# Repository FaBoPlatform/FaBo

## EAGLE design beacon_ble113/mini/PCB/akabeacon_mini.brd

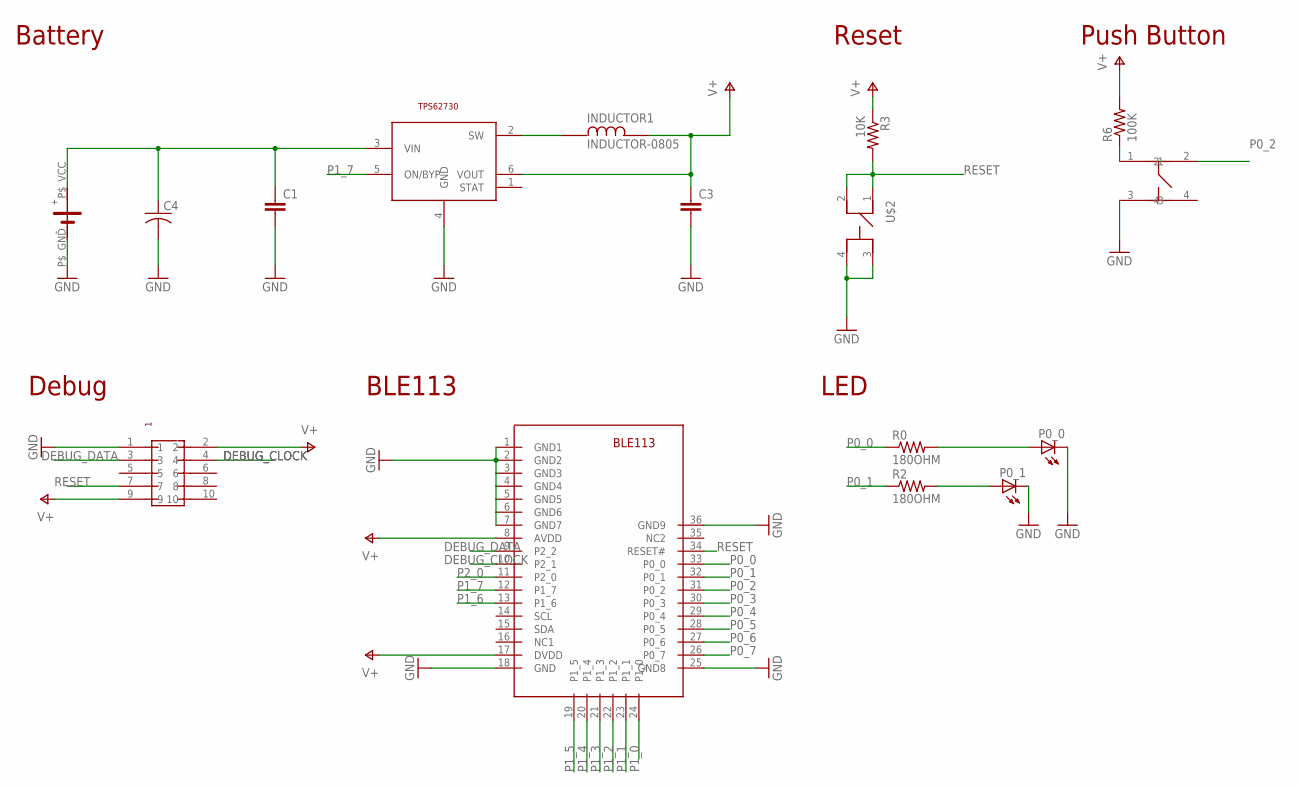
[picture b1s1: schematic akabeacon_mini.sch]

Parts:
C1, C3: C-EUC0603; C0603
C4: C-USC3225; C3225
INDUCTOR1: INDUCTOR-0805
P0_0, P0_1: LEDCHIP-LED0603; CHIP-LED0603
R0, R2: 180OHM; 0603-RES
R3: 10K; 0603-RES
R6: 100K; 0603-RES
TPS1: TI-TPS62730
U$1: SMTU2450-BOTTOM-MINI
U$2: SWITCH-LS6J2M-T
U$3: PIN-HEADER-SMT(1.27MM)2X5
U$4: BLE113
U$5: SWICTH-4P(KMR2); SWITCH-4P(KMR2)

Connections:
DEBUG_CLOCK: U$3.4, U$4.10 (P2_1)
DEBUG_DATA: U$3.3, U$4.9 (P2_2)
GND: C1.2, C3.2, C4.2, P0_0.C, P0_1.C, TPS1.4 (GND), U$1.P$_GND, U$2.3, U$2.4, U$3.1, U$4.1 (GND1), U$4.2 (GND2), U$4.3 (GND3), U$4.4 (GND4), U$4.5 (GND5), U$4.6 (GND6), U$4.7 (GND7), U$4.18 (GND), U$4.25 (GND8), U$4.36 (GND9), U$5.3
unnamed: C1.1, C4.1, TPS1.3 (VIN), U$1.P$_VCC
unnamed: P0_0.A, R0.2
unnamed: P0_1.A, R2.2
unnamed: INDUCTOR1.P$1, TPS1.2 (SW)
P0_0: R0.1, U$4.33 (P0_0)
P0_1: R2.1, U$4.32 (P0_1)
P0_2: R6.1, U$4.31 (P0_2), U$5.1
P0_3: U$4.30 (P0_3)
P0_4: U$4.29 (P0_4)
P0_5: U$4.28 (P0_5)
P0_6: U$4.27 (P0_6)
P0_7: U$4.26 (P0_7)
P1_0: U$4.24 (P1_0)
P1_1: U$4.23 (P1_1)
P1_2: U$4.22 (P1_2)
P1_3: U$4.21 (P1_3)
P1_4: U$4.20 (P1_4)
P1_5: U$4.19 (P1_5)
P1_6: U$4.13 (P1_6)
P1_7: TPS1.5 (ON/BYP), U$4.12 (P1_7)
P2_0: U$4.11 (P2_0)
RESET: R3.2, U$2.1, U$3.7, U$4.34 (RESET#)
V+: C3.1, INDUCTOR1.P$2, R3.1, R6.2, TPS1.6 (VOUT), U$3.2, U$3.9, U$4.8 (AVDD), U$4.17 (DVDD)

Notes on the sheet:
Reset
Battery
Push Button
Debug
BLE113
LED

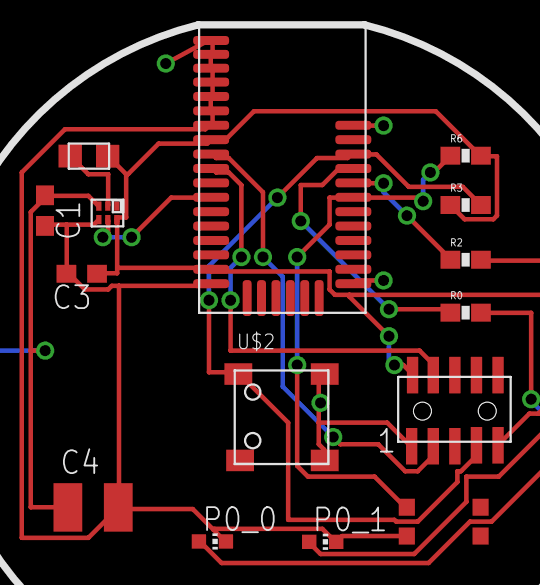
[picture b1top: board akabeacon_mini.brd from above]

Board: 2 copper layers, 16 parts (0 on the bottom side), 13 nets.

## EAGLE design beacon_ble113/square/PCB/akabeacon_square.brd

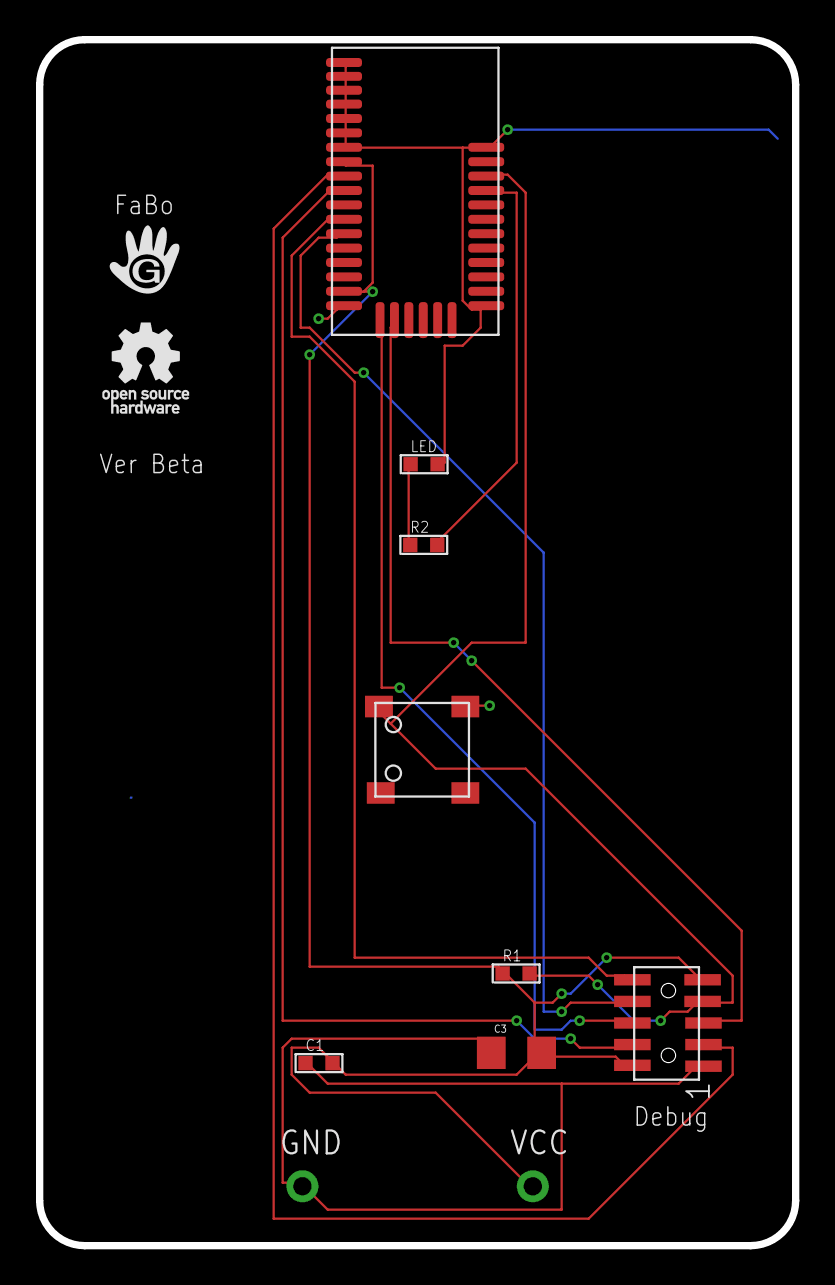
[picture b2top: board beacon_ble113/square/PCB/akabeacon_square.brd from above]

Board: 4 copper layers, 42.0 x 67.0 mm, 12 parts (0 on the bottom side), 11 nets.

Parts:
C1: 1u; 0603
C3: 100uF; 1206
GND: 1X01-CLEANBIG
LED: LED0603; 0603
R1, R2: 4.7K; 0603
U$2: PIN-HEADER-SMT(1.27MM)2X5
U$3: LOGO_FABO_M
U$4: LOGO_OSHW_T_M
U$5: BLE113
U$8: SWITCH-LS6J2M-T; SWICTH-LS6J2M-T
VCC: 1X01-CLEANBIG

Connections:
3.3V: C1.2, C3.2, R1.1, U$2.2, U$2.9, U$5.8, U$5.17, VCC.1
DEBUG_CLOCK: U$2.4, U$5.10
DEBUG_DATA: U$2.3, U$5.9
GND: C1.1, C3.1, GND.1, LED.CATHODE, U$2.1, U$5.1, U$5.2, U$5.3, U$5.4, U$5.5, U$5.6, U$5.7, U$5.18, U$5.25, U$5.36, U$8.3
unnamed: LED.ANODE, R2.1
P0_0: R2.2, U$5.33
P1_4: U$2.5, U$5.20
P1_5: U$2.6, U$5.19
P1_6: U$2.8, U$5.13
P1_7: U$2.10, U$5.12
RESET: R1.2, U$2.7, U$5.34, U$8.1

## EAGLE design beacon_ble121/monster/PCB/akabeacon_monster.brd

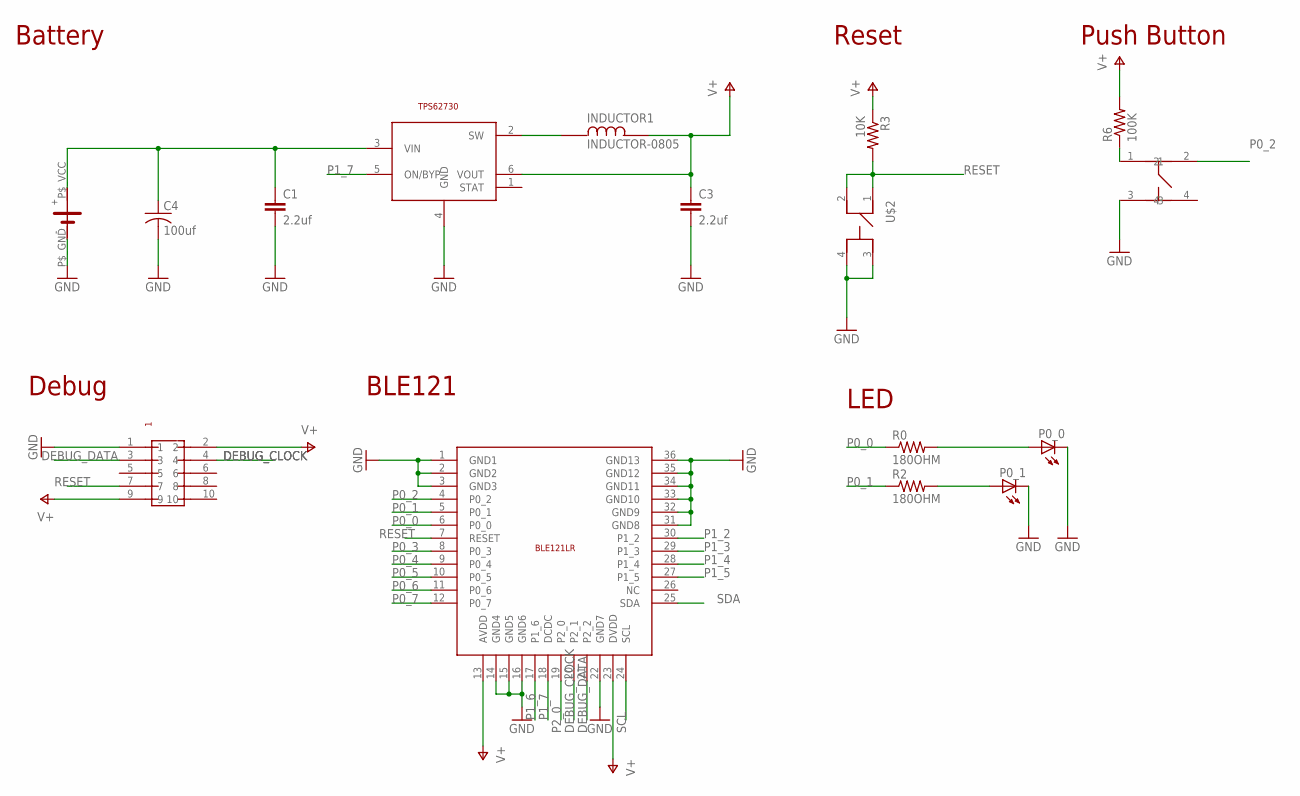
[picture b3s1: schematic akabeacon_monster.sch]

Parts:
BLE1: BLUEGIGA-BLE121LR
C1, C3: 2.2uf; C0603
C4: 100uf; C3225
INDUCTOR1: INDUCTOR-0805
P0_0, P0_1: LEDCHIP-LED0603; CHIP-LED0603
R0, R2: 180OHM; 0603-RES
R3: 10K; 0603-RES
R6: 100K; 0603-RES
TPS1: TI-TPS62730
U$1: SMTU2450-BOTTOM-MINI
U$2: SWITCH-LS6J2M-T
U$3: PIN-HEADER-SMT(1.27MM)2X5
U$5: SWICTH-4P(KMR2); SWITCH-4P(KMR2)

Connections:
DEBUG_CLOCK: BLE1.20 (P2_1), U$3.4
DEBUG_DATA: BLE1.21 (P2_2), U$3.3
GND: BLE1.1 (GND1), BLE1.2 (GND2), BLE1.3 (GND3), BLE1.22 (GND7), BLE1.31 (GND8), BLE1.32 (GND9), BLE1.33 (GND10), BLE1.34 (GND11), BLE1.35 (GND12), BLE1.36 (GND13), C1.2, C3.2, C4.2, P0_0.C, P0_1.C, TPS1.4 (GND), U$1.P$_GND, U$2.3, U$2.4, U$3.1, U$5.3
unnamed: C1.1, C4.1, TPS1.3 (VIN), U$1.P$_VCC
unnamed: P0_0.A, R0.2
unnamed: P0_1.A, R2.2
unnamed: INDUCTOR1.P$1, TPS1.2 (SW)
unnamed: BLE1.14 (GND4), BLE1.15 (GND5), BLE1.16 (GND6)
P0_0: BLE1.6 (P0_0), R0.1
P0_1: BLE1.5 (P0_1), R2.1
P0_2: BLE1.4 (P0_2), R6.1, U$5.1
P0_3: BLE1.8 (P0_3)
P0_4: BLE1.9 (P0_4)
P0_5: BLE1.10 (P0_5)
P0_6: BLE1.11 (P0_6)
P0_7: BLE1.12 (P0_7)
P1_2: BLE1.30 (P1_2)
P1_3: BLE1.29 (P1_3)
P1_4: BLE1.28 (P1_4)
P1_5: BLE1.27 (P1_5)
P1_6: BLE1.17 (P1_6)
P1_7: BLE1.18 (DCDC), TPS1.5 (ON/BYP)
P2_0: BLE1.19 (P2_0)
RESET: BLE1.7 (RESET), R3.2, U$2.1, U$2.2, U$3.7
SCL: BLE1.24 (SCL)
SDA: BLE1.25 (SDA)
V+: BLE1.13 (AVDD), BLE1.23 (DVDD), C3.1, INDUCTOR1.P$2, R3.1, R6.2, TPS1.6 (VOUT), U$3.2, U$3.9

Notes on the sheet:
Reset
Battery
Push Button
Debug
BLE121
LED

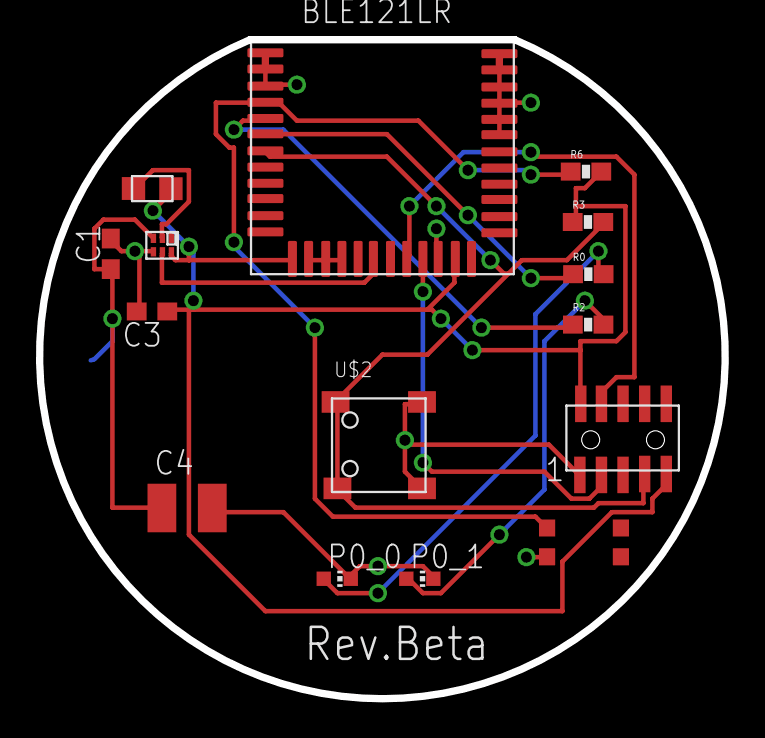
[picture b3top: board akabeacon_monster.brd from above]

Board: 2 copper layers, 38.1 x 36.6 mm, 16 parts (0 on the bottom side), 14 nets.

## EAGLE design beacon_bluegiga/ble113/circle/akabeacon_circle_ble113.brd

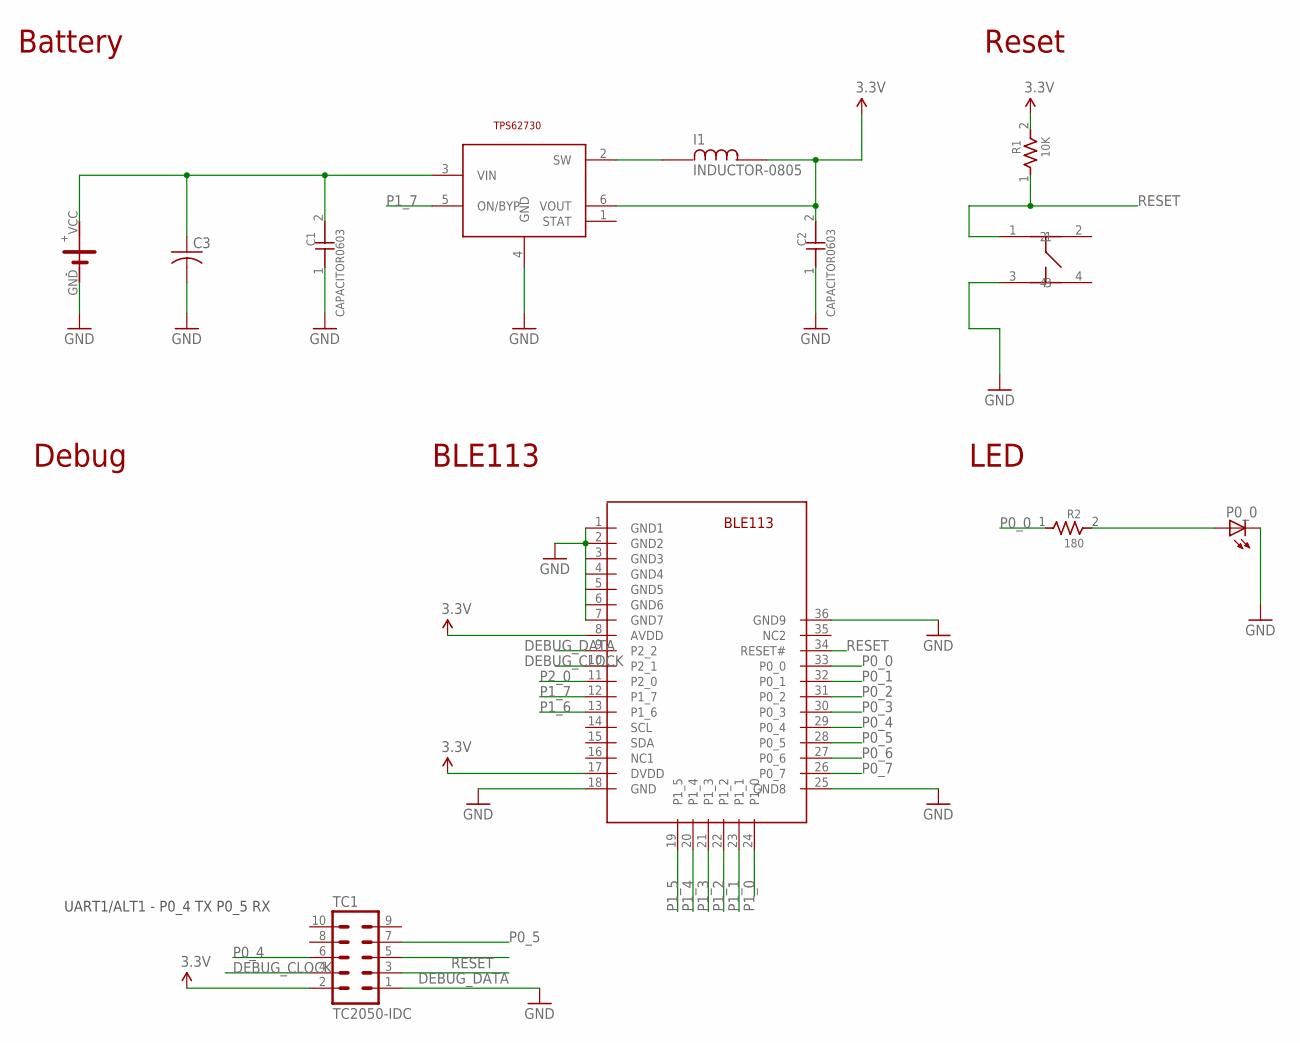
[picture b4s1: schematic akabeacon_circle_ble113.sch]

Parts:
C1, C2: CAPACITOR0603; 0603
C3: C-USC3225; C3225
I1: INDUCTOR-0805
P0_0: LEDCHIP-LED0603; CHIP-LED0603
R1: 10K; 0603
R2: 180; 0603
TC1: TC2050-IDC; TC2050-IDC-NL
TPS1: TI-TPS62730
U$1: CIRCLE-TYPE1; CIRCLE-TYE1-TC2030
U$4: BLE113
U$5: SWICTH-4P(KMR2); SWITCH-4P(KMR2)

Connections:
3.3V: C2.2, I1.P$2, R1.2, TC1.2, TPS1.6 (VOUT), U$4.8 (AVDD), U$4.17 (DVDD)
DEBUG_CLOCK: TC1.4, U$4.10 (P2_1)
DEBUG_DATA: TC1.3, U$4.9 (P2_2)
GND: C1.1, C2.1, C3.2, P0_0.C, TC1.1, TPS1.4 (GND), U$1.GND, U$4.1 (GND1), U$4.2 (GND2), U$4.3 (GND3), U$4.4 (GND4), U$4.5 (GND5), U$4.6 (GND6), U$4.7 (GND7), U$4.18 (GND), U$4.25 (GND8), U$4.36 (GND9), U$5.3
unnamed: C1.2, C3.1, TPS1.3 (VIN), U$1.VCC
unnamed: I1.P$1, TPS1.2 (SW)
P0_0: R2.1, U$4.33 (P0_0)
P0_1: U$4.32 (P0_1)
P0_2: U$4.31 (P0_2)
P0_3: U$4.30 (P0_3)
P0_4: TC1.6, U$4.29 (P0_4)
P0_5: TC1.7, U$4.28 (P0_5)
P0_6: U$4.27 (P0_6)
P0_7: U$4.26 (P0_7)
P1_0: U$4.24 (P1_0)
P1_1: U$4.23 (P1_1)
P1_2: U$4.22 (P1_2)
P1_3: U$4.21 (P1_3)
P1_4: U$4.20 (P1_4)
P1_5: U$4.19 (P1_5)
P1_6: U$4.13 (P1_6)
P1_7: TPS1.5 (ON/BYP), U$4.12 (P1_7)
P2_0: U$4.11 (P2_0)
R2: P0_0.A, R2.2
RESET: R1.1, TC1.5, U$4.34 (RESET#), U$5.1

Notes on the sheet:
Reset
Battery
Debug
BLE113
LED
UART1/ALT1 - P0_4 TX P0_5 RX

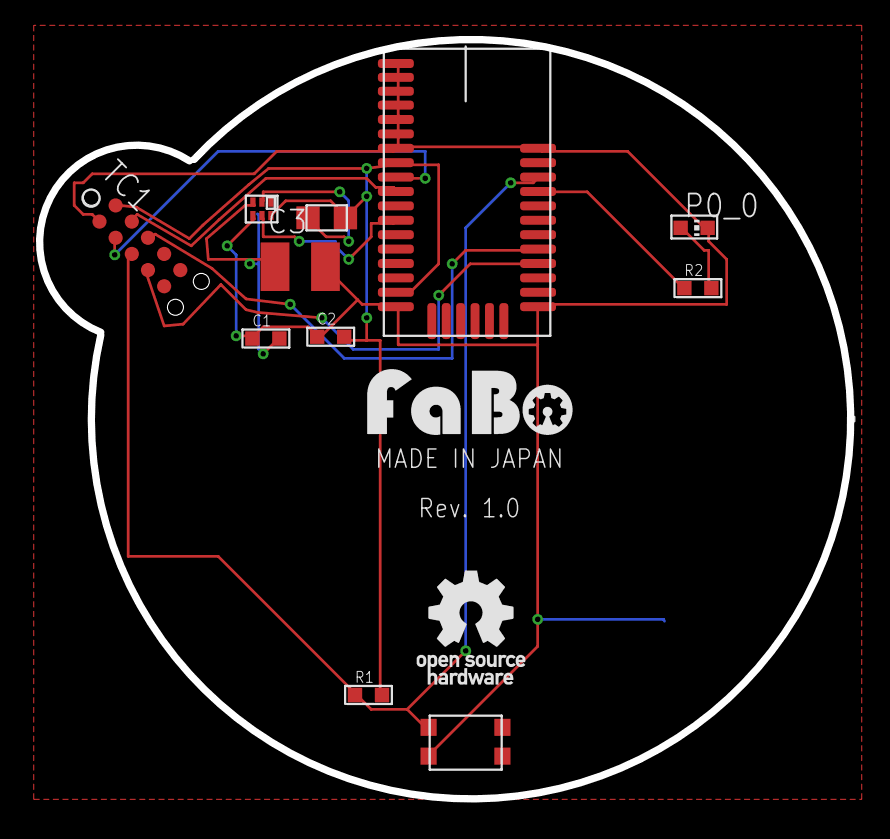
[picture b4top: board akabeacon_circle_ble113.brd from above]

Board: 2 copper layers, 14 parts (0 on the bottom side), 12 nets.

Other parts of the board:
U$2: LOGO_FABO_M
U$7: LOGO_OSHW_T_M

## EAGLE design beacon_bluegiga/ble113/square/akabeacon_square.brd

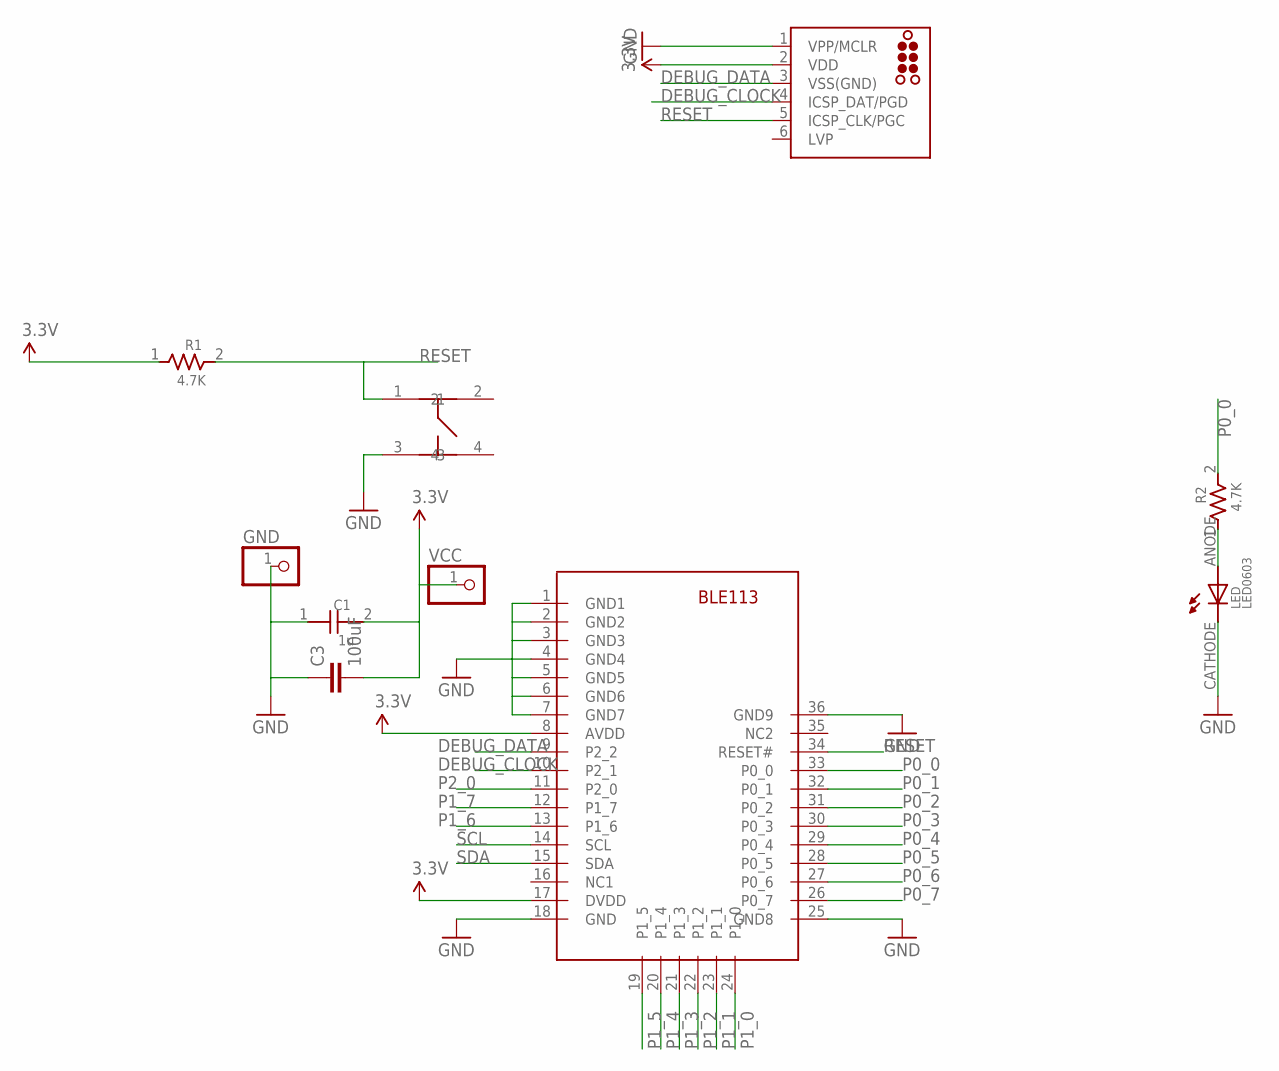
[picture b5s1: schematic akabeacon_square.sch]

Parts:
C1: 1u; 0603
C3: 100uF; 1206
GND: PINHD-1X1CB; 1X01-CLEANBIG
J1: TC2030-MCP
LED: LED0603; 0603
R1, R2: 4.7K; 0603
U$5: BLE113
U$6: SWICTH-4P(KMR2); SWITCH-4P(KMR2)
VCC: PINHD-1X1CB; 1X01-CLEANBIG

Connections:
3.3V: C1.2, C3.2, J1.2 (VDD), R1.1, U$5.8 (AVDD), U$5.17 (DVDD), VCC.1
DEBUG_CLOCK: J1.4 (ICSP_DAT/PGD), U$5.10 (P2_1)
DEBUG_DATA: J1.3 (VSS(GND)), U$5.9 (P2_2)
GND: C1.1, C3.1, GND.1, J1.1 (VPP/MCLR), LED.CATHODE, U$5.1 (GND1), U$5.2 (GND2), U$5.3 (GND3), U$5.4 (GND4), U$5.5 (GND5), U$5.6 (GND6), U$5.7 (GND7), U$5.18 (GND), U$5.25 (GND8), U$5.36 (GND9), U$6.3
unnamed: LED.ANODE, R2.1
P0_0: R2.2, U$5.33 (P0_0)
P0_1: U$5.32 (P0_1)
P0_2: U$5.31 (P0_2)
P0_3: U$5.30 (P0_3)
P0_4: U$5.29 (P0_4)
P0_5: U$5.28 (P0_5)
P0_6: U$5.27 (P0_6)
P0_7: U$5.26 (P0_7)
P1_0: U$5.24 (P1_0)
P1_1: U$5.23 (P1_1)
P1_2: U$5.22 (P1_2)
P1_3: U$5.21 (P1_3)
P1_4: U$5.20 (P1_4)
P1_5: U$5.19 (P1_5)
P1_6: U$5.13 (P1_6)
P1_7: U$5.12 (P1_7)
P2_0: U$5.11 (P2_0)
RESET: J1.5 (ICSP_CLK/PGC), R1.2, U$5.34 (RESET#), U$6.1
SCL: U$5.14 (SCL)
SDA: U$5.15 (SDA)

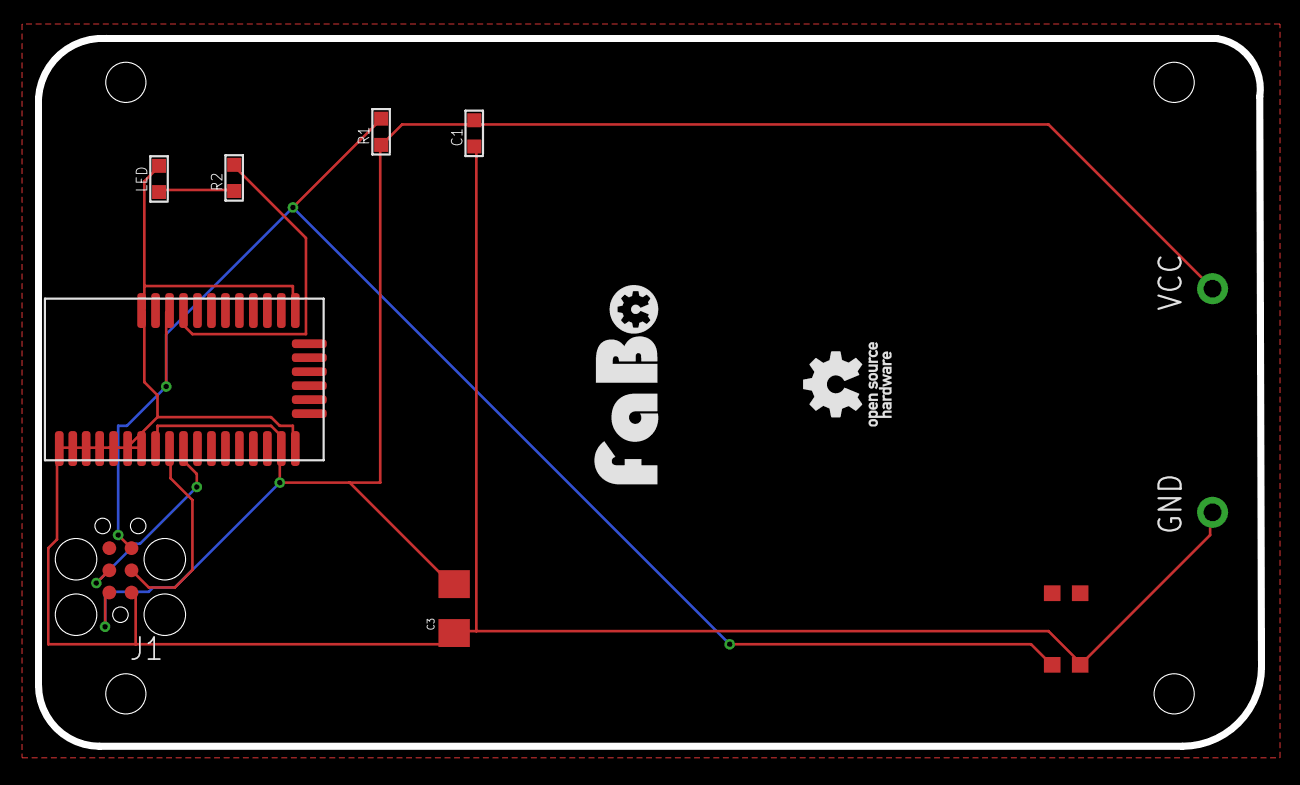
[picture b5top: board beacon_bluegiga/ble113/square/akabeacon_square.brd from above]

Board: 2 copper layers, 70.0 x 40.5 mm, 12 parts (0 on the bottom side), 7 nets.

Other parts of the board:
U$3: LOGO_FABO_M
U$4: LOGO_OSHW_T_M

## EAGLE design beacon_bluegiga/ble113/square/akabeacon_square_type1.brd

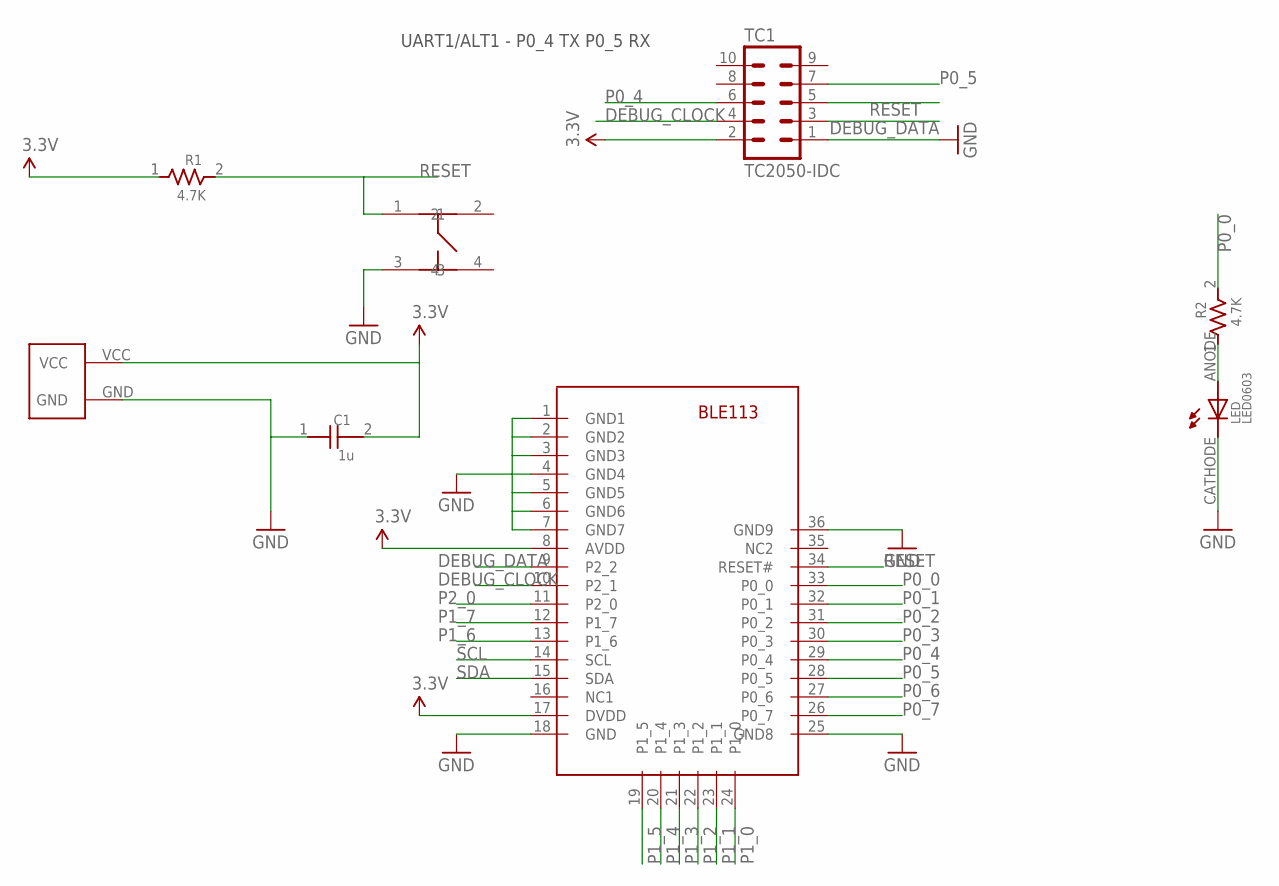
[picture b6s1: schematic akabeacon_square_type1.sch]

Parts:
C1: 1u; 0603
LED: LED0603; 0603
R1, R2: 4.7K; 0603
TC1: TC2050-IDC; TC2050-IDC-NL
U$2: SQUARE-TYPE1; SQUARE-TYPE1-TC2030
U$5: BLE113
U$6: SWICTH-4P(KMR2); SWITCH-4P(KMR2)

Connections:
3.3V: C1.2, R1.1, TC1.2, U$2.VCC, U$5.8 (AVDD), U$5.17 (DVDD)
DEBUG_CLOCK: TC1.4, U$5.10 (P2_1)
DEBUG_DATA: TC1.3, U$5.9 (P2_2)
GND: C1.1, LED.CATHODE, TC1.1, U$2.GND, U$5.1 (GND1), U$5.2 (GND2), U$5.3 (GND3), U$5.4 (GND4), U$5.5 (GND5), U$5.6 (GND6), U$5.7 (GND7), U$5.18 (GND), U$5.25 (GND8), U$5.36 (GND9), U$6.3
unnamed: LED.ANODE, R2.1
P0_0: R2.2, U$5.33 (P0_0)
P0_1: U$5.32 (P0_1)
P0_2: U$5.31 (P0_2)
P0_3: U$5.30 (P0_3)
P0_4: TC1.6, U$5.29 (P0_4)
P0_5: TC1.7, U$5.28 (P0_5)
P0_6: U$5.27 (P0_6)
P0_7: U$5.26 (P0_7)
P1_0: U$5.24 (P1_0)
P1_1: U$5.23 (P1_1)
P1_2: U$5.22 (P1_2)
P1_3: U$5.21 (P1_3)
P1_4: U$5.20 (P1_4)
P1_5: U$5.19 (P1_5)
P1_6: U$5.13 (P1_6)
P1_7: U$5.12 (P1_7)
P2_0: U$5.11 (P2_0)
RESET: R1.2, TC1.5, U$5.34 (RESET#), U$6.1
SCL: U$5.14 (SCL)
SDA: U$5.15 (SDA)

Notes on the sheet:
UART1/ALT1 - P0_4 TX P0_5 RX

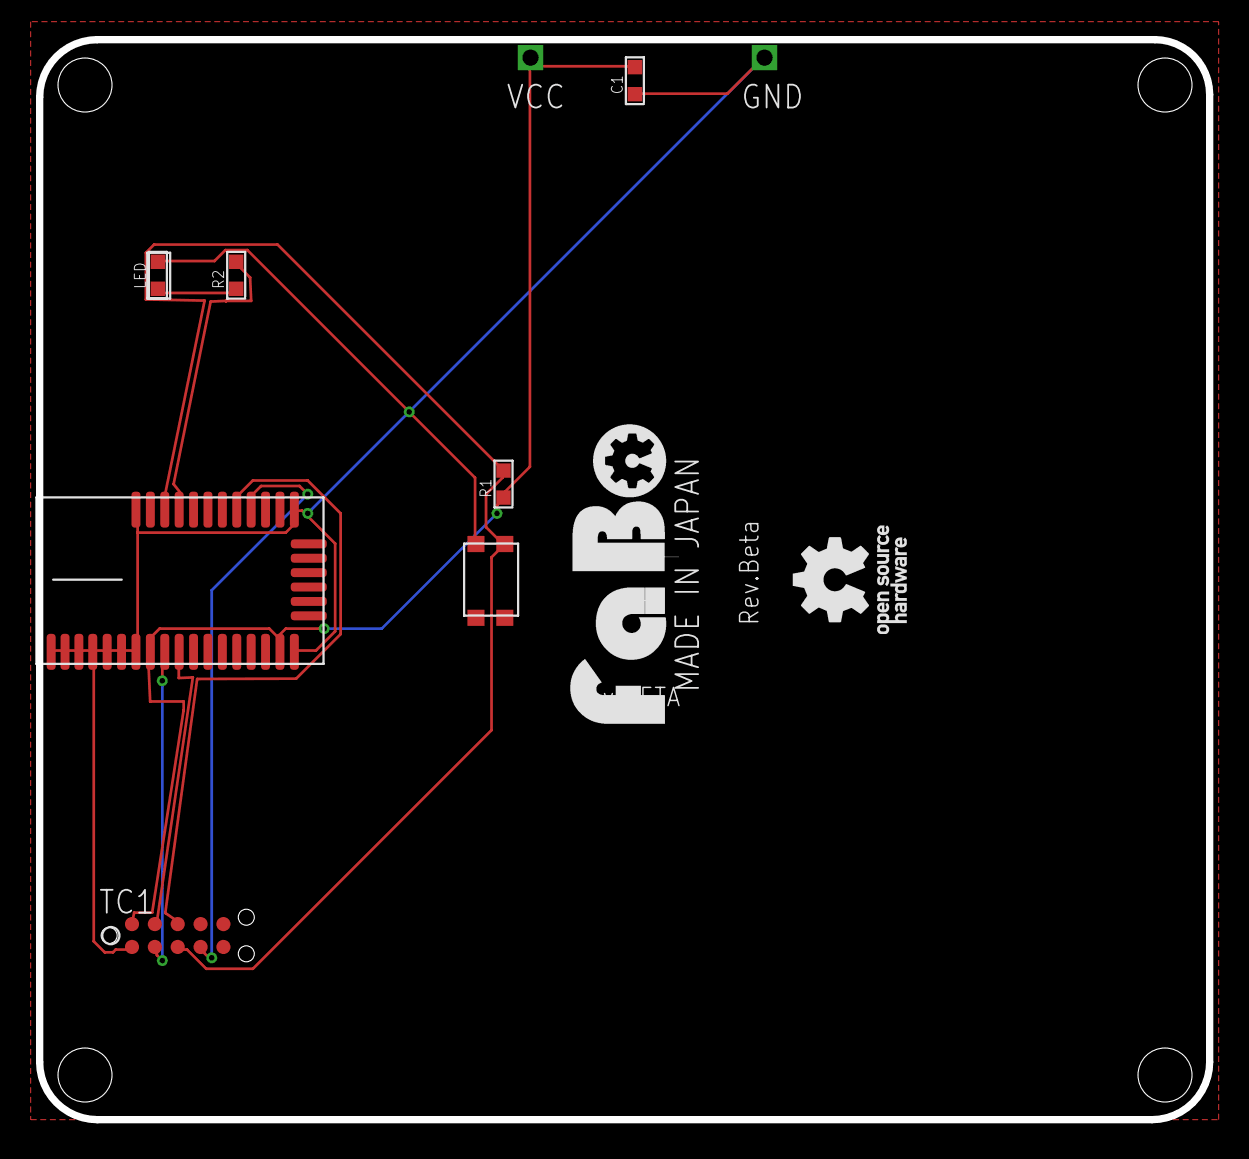
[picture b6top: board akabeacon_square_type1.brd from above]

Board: 2 copper layers, 65.0 x 60.0 mm, 8 parts (0 on the bottom side), 9 nets.

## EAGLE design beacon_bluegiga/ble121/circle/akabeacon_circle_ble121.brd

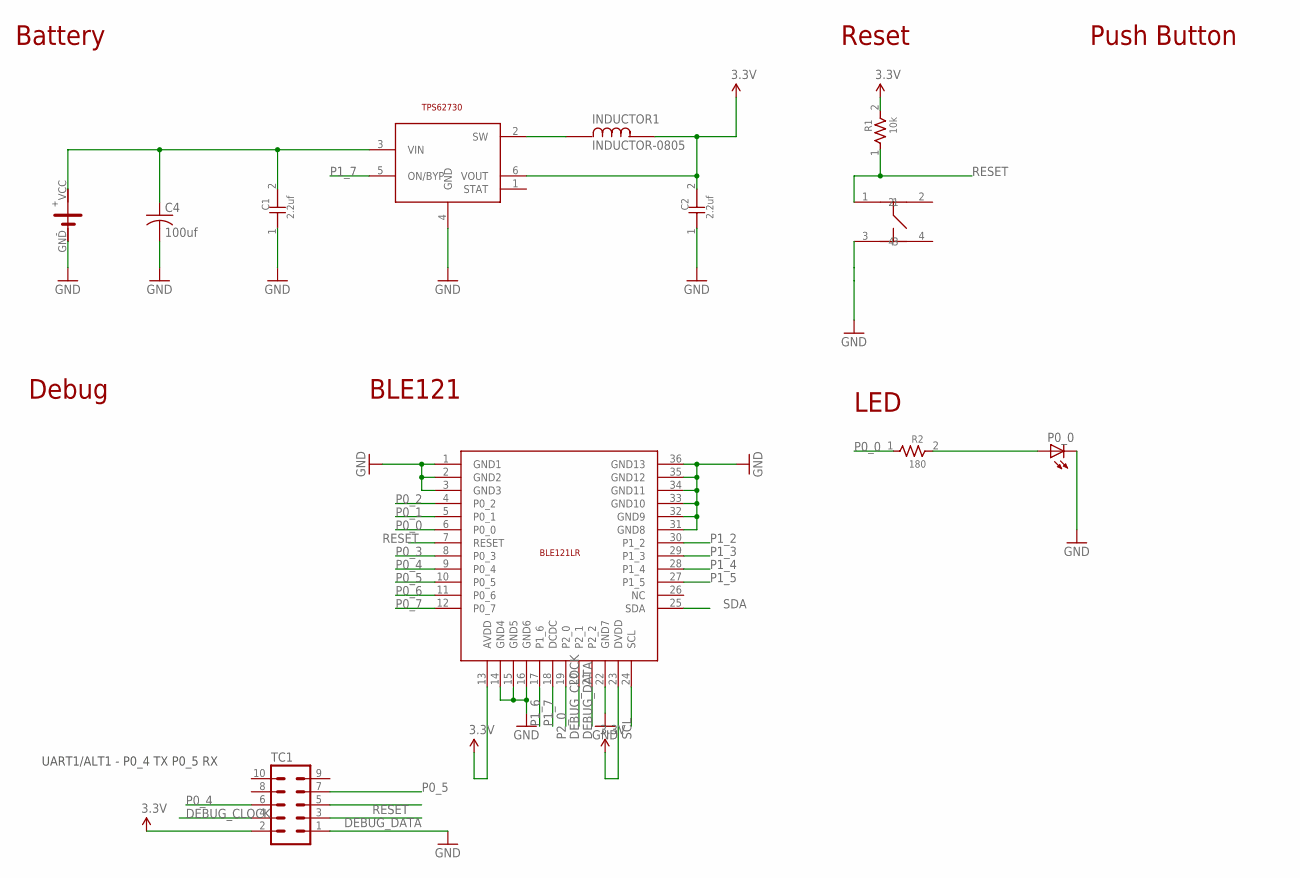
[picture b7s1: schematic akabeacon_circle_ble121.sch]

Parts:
BLE1: BLUEGIGA-BLE121LR
C1, C2: 2.2uf; 0603
C4: 100uf; C3225
INDUCTOR1: INDUCTOR-0805
P0_0: LEDCHIP-LED0603; CHIP-LED0603
R1: 10k; 0603
R2: 180; 0603
TC1: TC2050-IDC-NL
TPS1: TI-TPS62730
U$1: CIRCLE-TYPE1; CIRCLE-TYE1-TC2030
U$5: SWICTH-4P(KMR2); SWITCH-4P(KMR2)

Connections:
3.3V: BLE1.13 (AVDD), BLE1.23 (DVDD), C2.2, INDUCTOR1.P$2, R1.2, TC1.2, TPS1.6 (VOUT)
DEBUG_CLOCK: BLE1.20 (P2_1), TC1.4
DEBUG_DATA: BLE1.21 (P2_2), TC1.3
GND: BLE1.1 (GND1), BLE1.2 (GND2), BLE1.3 (GND3), BLE1.22 (GND7), BLE1.31 (GND8), BLE1.32 (GND9), BLE1.33 (GND10), BLE1.34 (GND11), BLE1.35 (GND12), BLE1.36 (GND13), C1.1, C2.1, C4.2, P0_0.C, TC1.1, TPS1.4 (GND), U$1.GND, U$5.3
unnamed: C1.2, C4.1, TPS1.3 (VIN), U$1.VCC
unnamed: P0_0.A, R2.2
unnamed: INDUCTOR1.P$1, TPS1.2 (SW)
unnamed: BLE1.14 (GND4), BLE1.15 (GND5), BLE1.16 (GND6)
P0_0: BLE1.6 (P0_0), R2.1
P0_1: BLE1.5 (P0_1)
P0_2: BLE1.4 (P0_2)
P0_3: BLE1.8 (P0_3)
P0_4: BLE1.9 (P0_4), TC1.6
P0_5: BLE1.10 (P0_5), TC1.7
P0_6: BLE1.11 (P0_6)
P0_7: BLE1.12 (P0_7)
P1_2: BLE1.30 (P1_2)
P1_3: BLE1.29 (P1_3)
P1_4: BLE1.28 (P1_4)
P1_5: BLE1.27 (P1_5)
P1_6: BLE1.17 (P1_6)
P1_7: BLE1.18 (DCDC), TPS1.5 (ON/BYP)
P2_0: BLE1.19 (P2_0)
RESET: BLE1.7 (RESET), R1.1, TC1.5, U$5.1
SCL: BLE1.24 (SCL)
SDA: BLE1.25 (SDA)

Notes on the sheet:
Reset
Battery
Push Button
Debug
BLE121
LED
UART1/ALT1 - P0_4 TX P0_5 RX

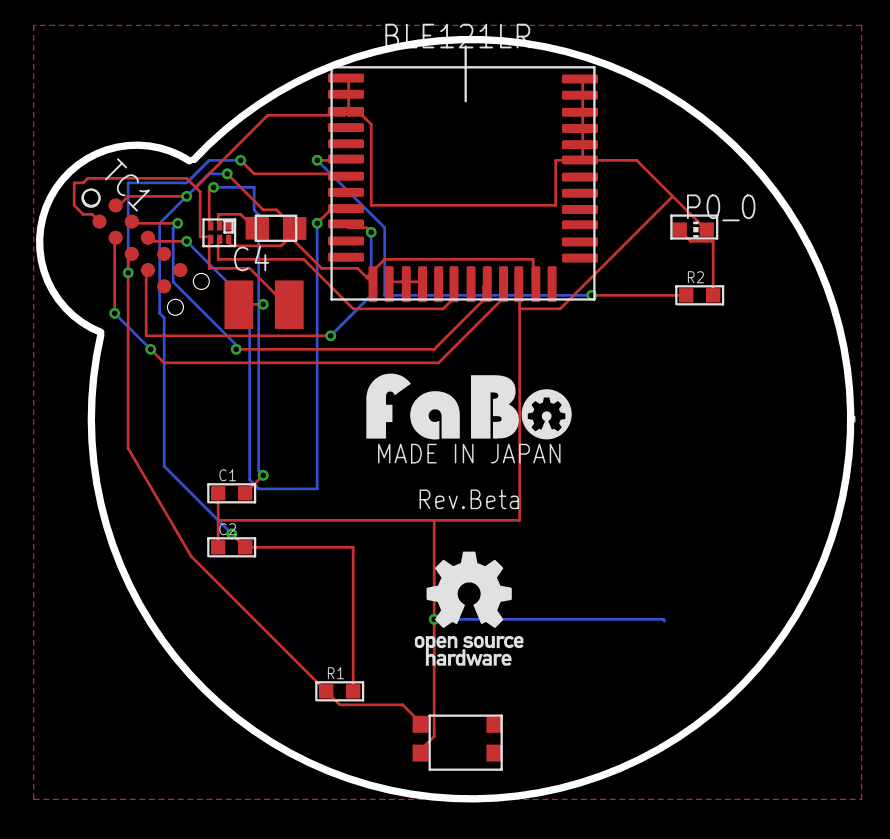
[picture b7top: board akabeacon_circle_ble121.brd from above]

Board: 2 copper layers, 14 parts (0 on the bottom side), 13 nets.

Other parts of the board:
U$2: LOGO_FABO_M
U$4: LOGO_OSHW_T_M

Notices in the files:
parts and their libraries:
SparkFun: Licensing: CC v3.0 Share-Alike You are welcome to use this library for commercial purposes.
SparkFun-Capacitors: Licensing: Creative Commons ShareAlike 4.0 International - https://creativecommons.org/licenses/by-sa/4.0
